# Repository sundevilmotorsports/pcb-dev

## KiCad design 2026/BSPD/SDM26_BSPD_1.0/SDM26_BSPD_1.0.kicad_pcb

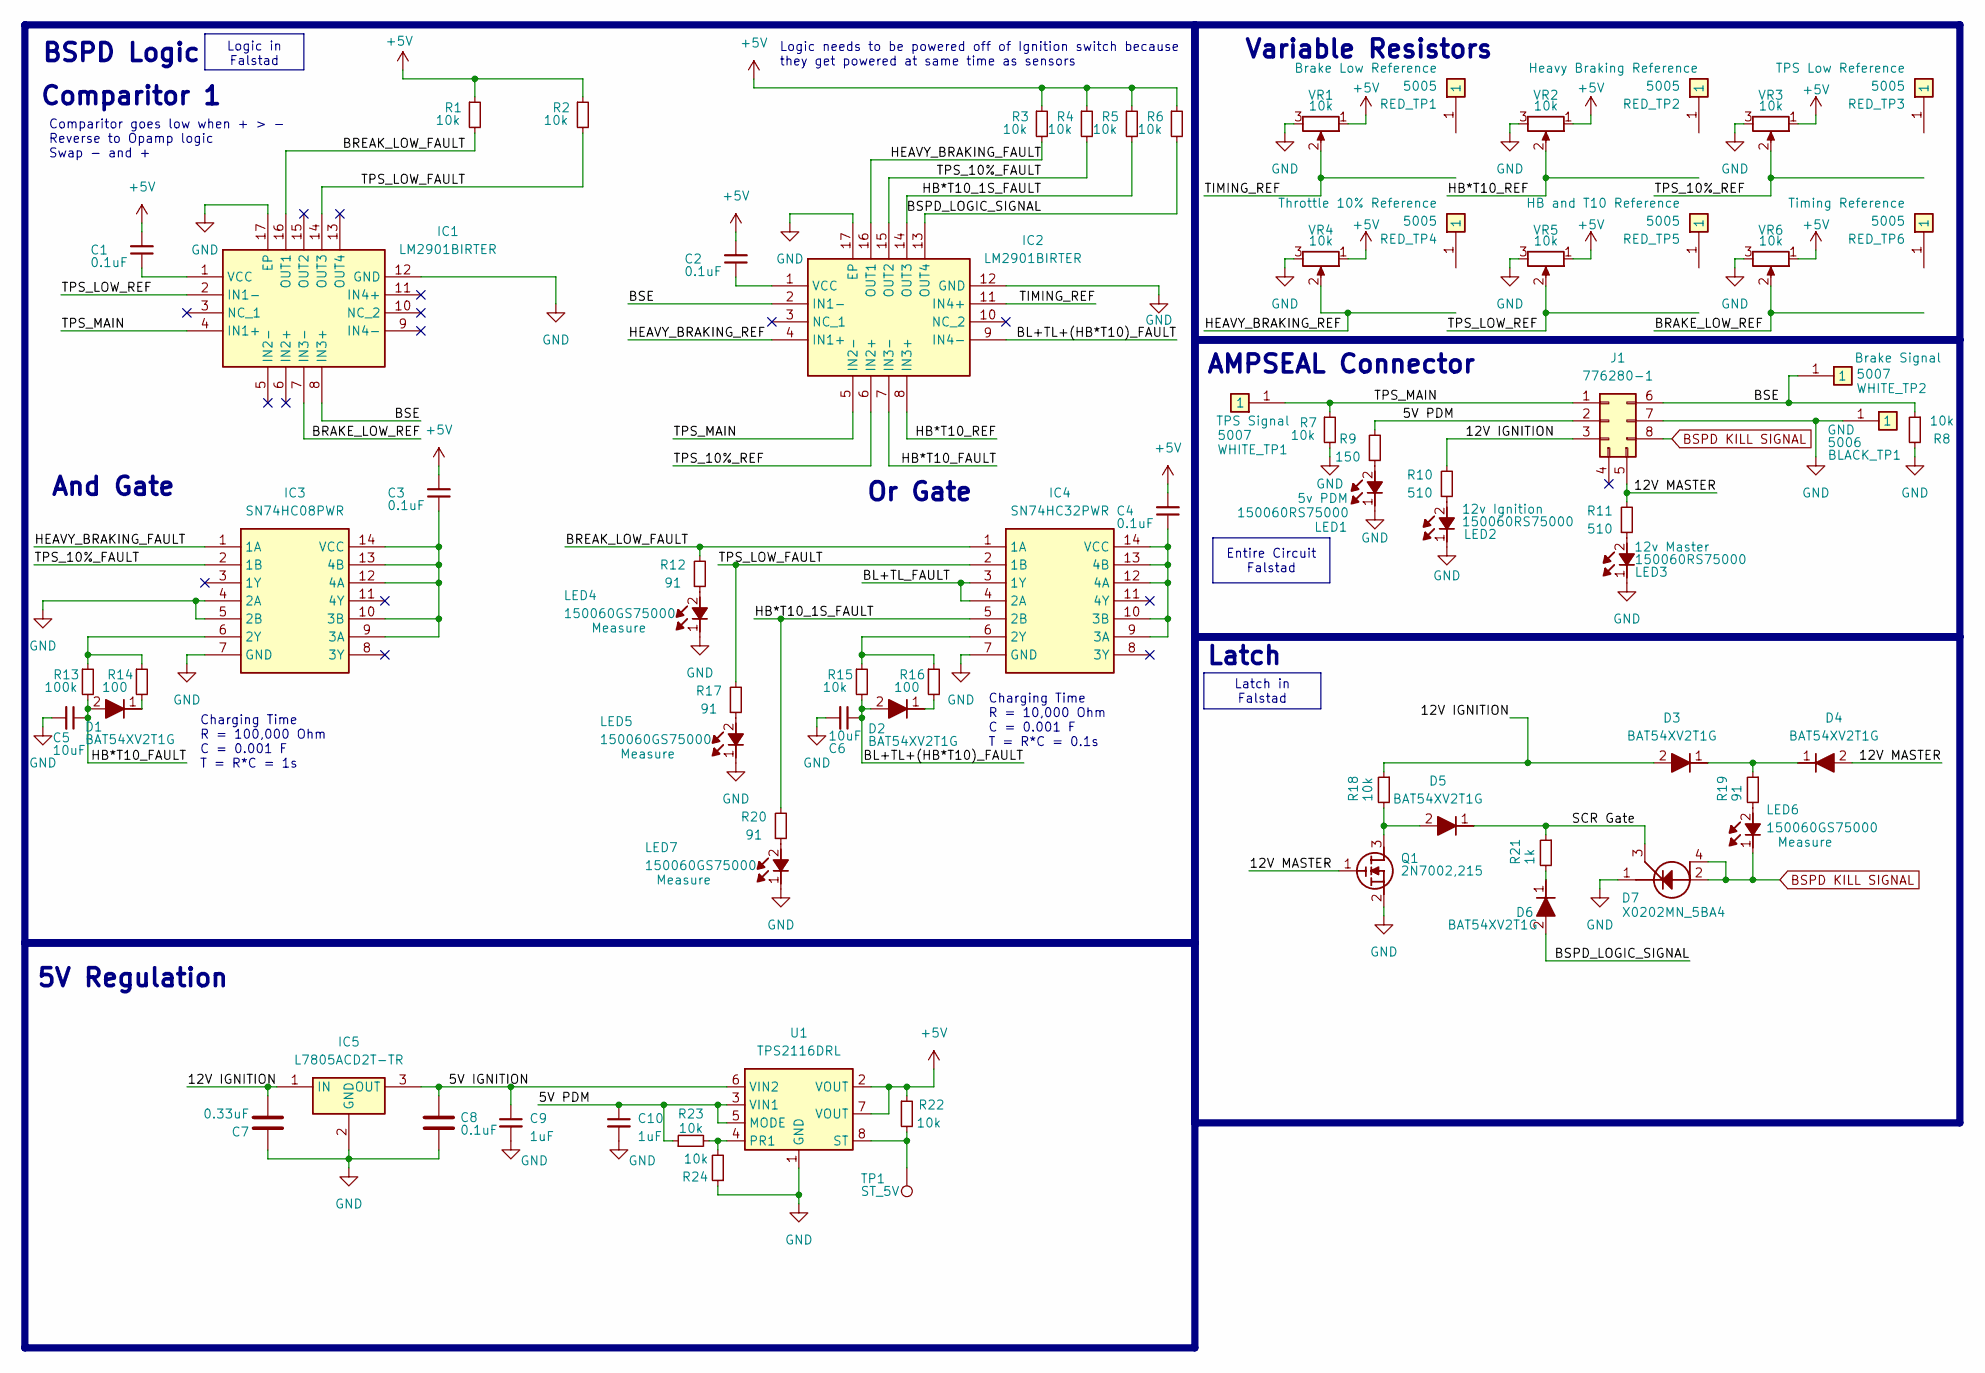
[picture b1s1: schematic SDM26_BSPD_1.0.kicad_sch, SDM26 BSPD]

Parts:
BLACK_TP1: 5006; Mouser Part Number 534-5006
C1, C2, C3, C4, C8: 0.1uF; C_0603_1608Metric
C5, C6: 10uF; C_0603_1608Metric
C7: 0.33uF; C_0603_1608Metric
C9, C10: 1uF; C_0603_1608Metric
D1, D2, D3, D4, D5, D6: BAT54XV2T1G; SODFL1608X70N; Mouser Part Number 863-BAT54XV2T1G
D7: X0202MN_5BA4; SOT230P700X190-4N; Mouser Part Number 511-X0202MN
IC1, IC2: LM2901BIRTER; QFN50P300X300X80-17N-D; Mouser Part Number 595-LM2901BIRTER
IC3: SN74HC08PWR; SOP65P640X120-14L; Mouser Part Number 595-SN74HC08PWR
IC4: SN74HC32PWR; SOP65P640X120-14L; Mouser Part Number 595-SN74HC32PWR
IC5: L7805ACD2T-TR; L7805ACD2TTR; Mouser Part Number 511-L7805ACD2T-TR
J1: 776280-1; Mouser Part Number 571-776280-1
LED1, LED2, LED3: 150060RS75000; LEDC1608X80N; Mouser Part Number 710-150060RS75000
LED4, LED5, LED6, LED7: 150060GS75000; LEDC1608X80N; Mouser Part Number 710-150060GS75000
Q1: 2N7002,215; SOT95P230X110-3N; Mouser Part Number 771-2N7002-T/R
R1, R2, R3, R4, R5, R6, R7, R8, R15, R18, R22, R23, R24: 10k; R_0603_1608Metric
R9: 150; R_0603_1608Metric
R10, R11: 510; R_0603_1608Metric
R12, R17, R19, R20: 91; R_0603_1608Metric
R13: 100k; R_0603_1608Metric
R14, R16: 100; R_0603_1608Metric
R21: 1k; R_0603_1608Metric
RED_TP1, RED_TP2, RED_TP3, RED_TP4, RED_TP5, RED_TP6: 5005; Mouser Part Number 534-5005
TP1: ST_5V; TestPoint_Pad_1.5x1.5mm
U1: TPS2116DRL; SOT-583-8
VR1, VR2, VR3, VR4, VR5, VR6: 10k; 3386P1103TLF; Mouser Part Number 652-3386P-1-103TLF
WHITE_TP1, WHITE_TP2: 5007; Mouser Part Number 534-5007

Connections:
+5V: C1.2, C2.2, C3.2, C4.2, R1.1, R2.1, R3.1, R4.1, R5.1, R6.1, R22.1, U1.2 (VOUT), U1.7 (VOUT), VR1.1 (CCW), VR2.1 (CCW), VR3.1 (CCW), VR4.1 (CCW), VR5.1 (CCW), VR6.1 (CCW)
/5V IGNITION: C8.2, C9.1, IC5.3 (OUT), U1.6 (VIN2)
/5V PDM: C10.1, J1.2, R9.2, R23.1, U1.3 (VIN1), U1.5 (MODE)
/12V IGNITION: C7.2, D3.2 (A), IC5.1 (IN), J1.3, R10.2, R18.1
/12V MASTER: D4.2 (A), J1.5, Q1.1 (G), R11.2
/BL+TL+(HB*T10)_FAULT: C6.1, D2.2 (A), IC2.9 (IN4-), R15.2
/BL+TL_FAULT: IC4.3 (1Y), IC4.4 (2A)
/BRAKE_LOW_REF: IC1.7 (IN3-), VR6.2 (Wiper)
/BREAK_LOW_FAULT: IC1.16 (OUT1), IC4.1 (1A), R1.2, R12.2
/BSE: IC1.8 (IN3+), IC2.2 (IN1-), J1.6, R8.1, WHITE_TP2.1
/BSPD_LOGIC_SIGNAL: D6.2 (A), IC2.13 (OUT4), R6.2
/HB*T10_1S_FAULT: IC2.14 (OUT3), IC4.5 (2B), R5.2, R20.2
/HB*T10_FAULT: C5.1, D1.2 (A), IC2.7 (IN3-), R13.2
/HB*T10_REF: IC2.8 (IN3+), VR2.2 (Wiper)
/HEAVY_BRAKING_FAULT: IC2.16 (OUT1), IC3.1 (1A), R3.2
/HEAVY_BRAKING_REF: IC2.4 (IN1+), VR4.2 (Wiper)
/SCR Gate: D5.1 (K), D7.3 (G), R21.1
/TIMING_REF: IC2.11 (IN4+), VR1.2 (Wiper)
/TPS_10%_FAULT: IC2.15 (OUT2), IC3.2 (1B), R4.2
/TPS_10%_REF: IC2.6 (IN2+), VR3.2 (Wiper)
/TPS_LOW_FAULT: IC1.14 (OUT3), IC4.2 (1B), R2.2, R17.2
/TPS_LOW_REF: IC1.2 (IN1-), VR5.2 (Wiper)
/TPS_MAIN: IC1.4 (IN1+), IC2.5 (IN2-), J1.1, R7.1, WHITE_TP1.1
BSPD KILL SIGNAL: D7.2 (A_1), D7.4 (A_2), J1.8, LED6.1 (K)
GND: BLACK_TP1.1, C5.2, C6.2, C7.1, C8.1, C9.2, C10.2, D7.1 (K), IC1.12 (GND), IC1.17 (EP), IC2.12 (GND), IC2.17 (EP), IC3.4 (2A), IC3.5 (2B), IC3.7 (GND), IC4.7 (GND), IC5.2 (GND), J1.7, LED1.1 (K), LED2.1 (K), LED3.1 (K), LED4.1 (K), LED5.1 (K), LED7.1 (K), Q1.2 (S), R7.2, R8.2, R24.1, U1.1 (GND), VR1.3 (CW), VR2.3 (CW), VR3.3 (CW), VR4.3 (CW), VR5.3 (CW), VR6.3 (CW)
unnamed: D1.1 (K), R14.2
unnamed: D2.1 (K), R16.2
unnamed: D3.1 (K), D4.1 (K), R19.1
unnamed: D5.2 (A), Q1.3 (D), R18.2
unnamed: D6.1 (K), R21.2
unnamed: C1.1, IC1.1 (VCC)
unnamed: C2.1, IC2.1 (VCC)
unnamed: IC3.6 (2Y), R13.1, R14.1
unnamed: C3.1, IC3.9 (3A), IC3.10 (3B), IC3.12 (4A), IC3.13 (4B), IC3.14 (VCC)
unnamed: IC4.6 (2Y), R15.1, R16.1
unnamed: C4.1, IC4.9 (3A), IC4.10 (3B), IC4.12 (4A), IC4.13 (4B), IC4.14 (VCC)
unnamed: LED1.2 (A), R9.1
unnamed: LED2.2 (A), R10.1
unnamed: LED3.2 (A), R11.1
unnamed: LED4.2 (A), R12.1
unnamed: LED5.2 (A), R17.1
unnamed: LED6.2 (A), R19.2
unnamed: LED7.2 (A), R20.1
unnamed: R23.2, R24.2, U1.4 (PR1)
unnamed: R22.2, TP1.1, U1.8 (ST)

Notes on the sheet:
5V Regulation
Latch
And Gate
Comparitor goes low when + > - Reverse to Opamp logic Swap - and +
Variable Resistors
Logic needs to be powered off of Ignition switch because they get powered at same time as sensors
Charging Time R = 100,000 Ohm C = 0.001 F T = R*C = 1s
Charging Time R = 10,000 Ohm C = 0.001 F T = R*C = 0.1s
AMPSEAL Connector
BSPD Logic
Or Gate
Comparitor 1
Latch in Falstad
Entire Circuit Falstad
Logic in Falstad

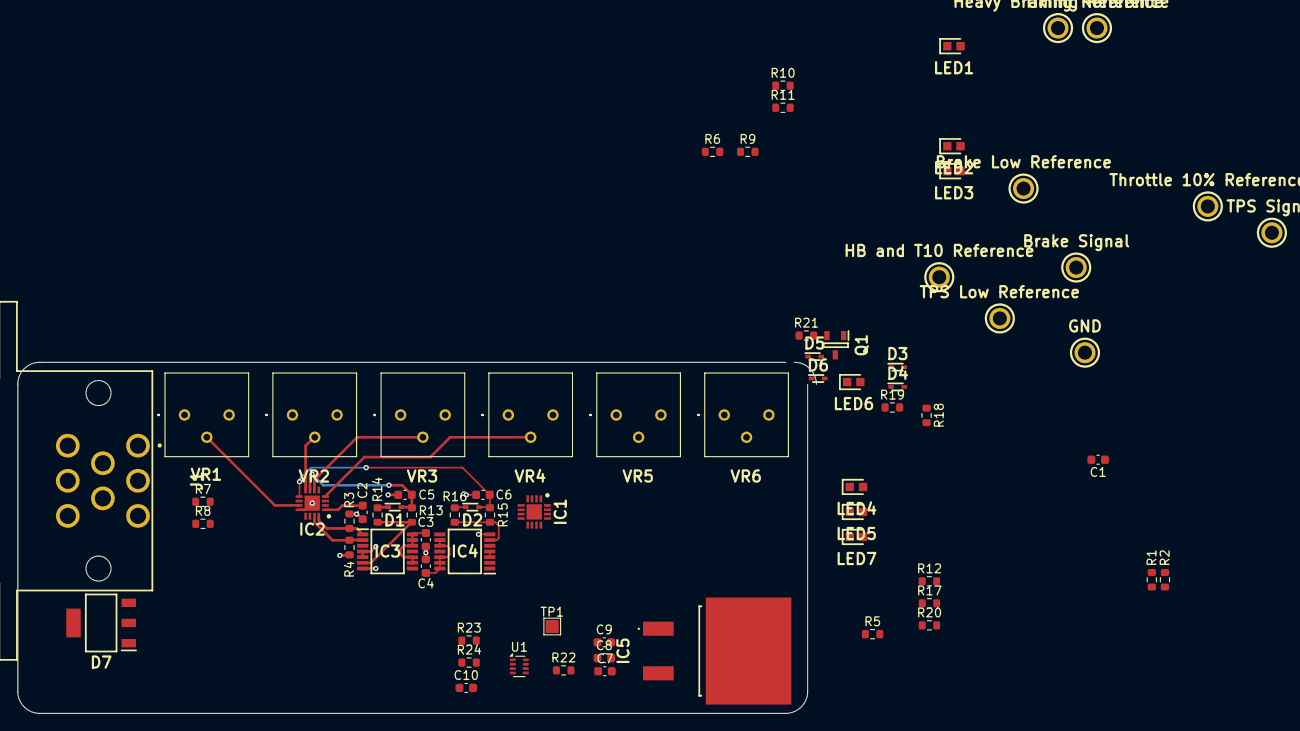
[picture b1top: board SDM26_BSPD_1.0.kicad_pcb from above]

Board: 4 copper layers, 91.0 x 40.0 mm, 72 parts (0 on the bottom side), 45 nets.

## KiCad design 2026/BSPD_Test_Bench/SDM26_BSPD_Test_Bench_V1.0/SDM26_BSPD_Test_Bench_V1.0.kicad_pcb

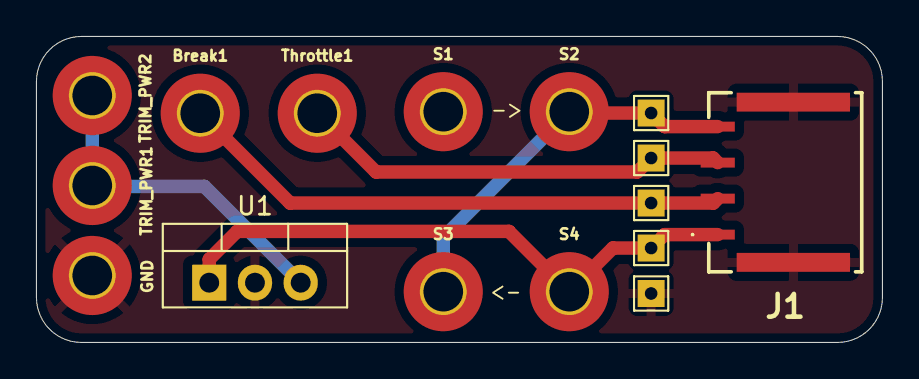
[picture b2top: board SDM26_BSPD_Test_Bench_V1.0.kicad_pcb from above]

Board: 2 copper layers, 47.0 x 17.0 mm, 11 parts (0 on the bottom side), 6 nets.

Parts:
Break1: MountingHole_Pad_MP; MountingHole_2.2mm_M2_Pad_TopBottom
GND: MountingHole_Pad_MP; MountingHole_2.2mm_M2_Pad_TopBottom
J1: SM04B-ULHK-1TA1-ETB_HF_; SM04BULHK1TA1ETBHF
S1, S2, S3, S4: MountingHole_Pad_MP; MountingHole_2.2mm_M2_Pad_TopBottom
TRIM_PWR1, TRIM_PWR2: MountingHole_Pad_MP; MountingHole_2.2mm_M2_Pad_TopBottom
Throttle1: MountingHole_Pad_MP; MountingHole_2.2mm_M2_Pad_TopBottom
U1: SPX2920U-5.0_TO220; TO-220-3_Vertical

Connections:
/Break: Break1.1, J1.2
/Throttle: J1.3, Throttle1.1
GND: GND.1, J1.5 (MP1), J1.6 (MP2), U1.2 (GND)
IGNPWR: J1.1, S4.1, U1.1 (VI)
MASTERPWR: J1.4, S2.1, S3.1
unnamed: TRIM_PWR1.1, TRIM_PWR2.1, U1.3 (VO)

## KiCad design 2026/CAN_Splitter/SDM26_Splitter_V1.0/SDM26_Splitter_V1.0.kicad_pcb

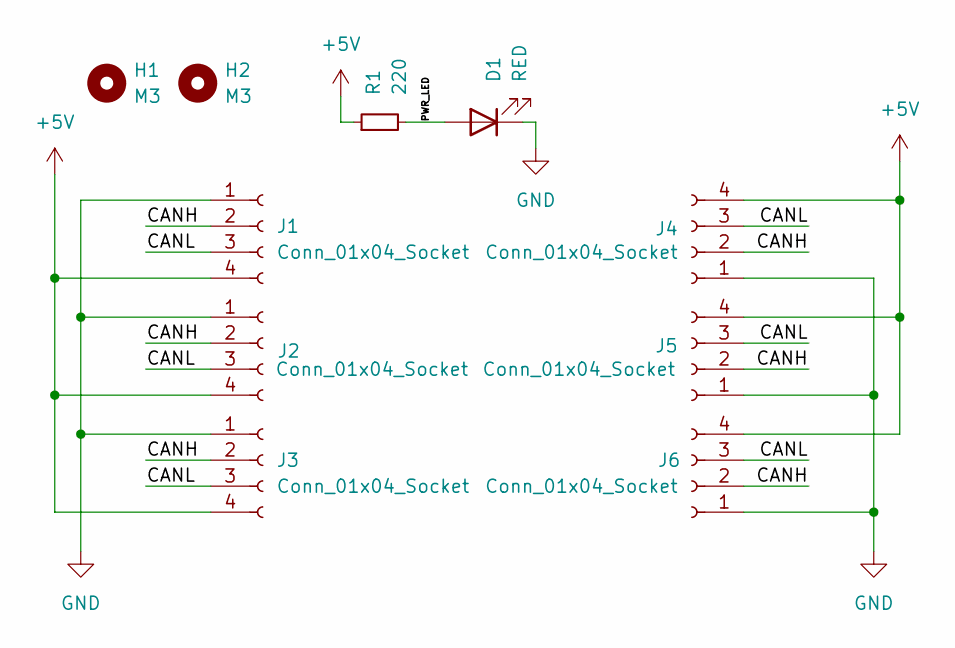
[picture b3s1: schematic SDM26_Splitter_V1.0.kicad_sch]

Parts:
D1: RED; LED_1206_3216Metric
H1, H2: M3; MountingHole_3.2mm_M3
J1, J2, J3, J4, J5, J6: Conn_01x04_Socket; JST_EH_S4B-EH_1x04_P2.50mm_Horizontal
R1: 220; C_0603_1608Metric

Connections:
+5V: J1.4, J2.4, J3.4, J4.4, J5.4, J6.4, R1.1
/CANH: J1.2, J2.2, J3.2, J4.2, J5.2, J6.2
/CANL: J1.3, J2.3, J3.3, J4.3, J5.3, J6.3
/PWR_LED: D1.2 (A), R1.2
GND: D1.1 (K), J1.1, J2.1, J3.1, J4.1, J5.1, J6.1

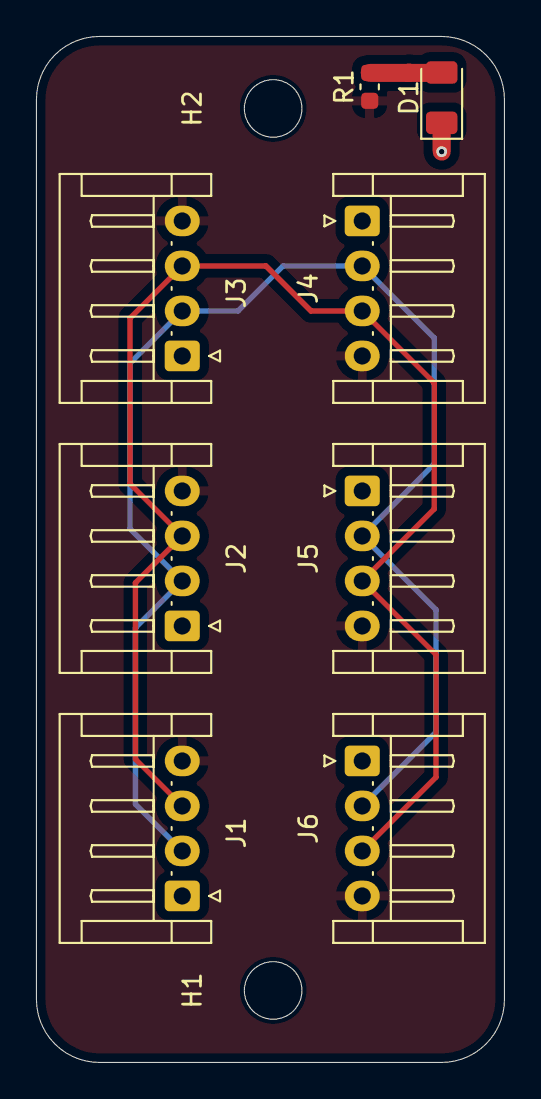
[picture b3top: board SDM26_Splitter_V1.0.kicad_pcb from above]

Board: 2 copper layers, 26.0 x 57.0 mm, 10 parts (0 on the bottom side), 5 nets.

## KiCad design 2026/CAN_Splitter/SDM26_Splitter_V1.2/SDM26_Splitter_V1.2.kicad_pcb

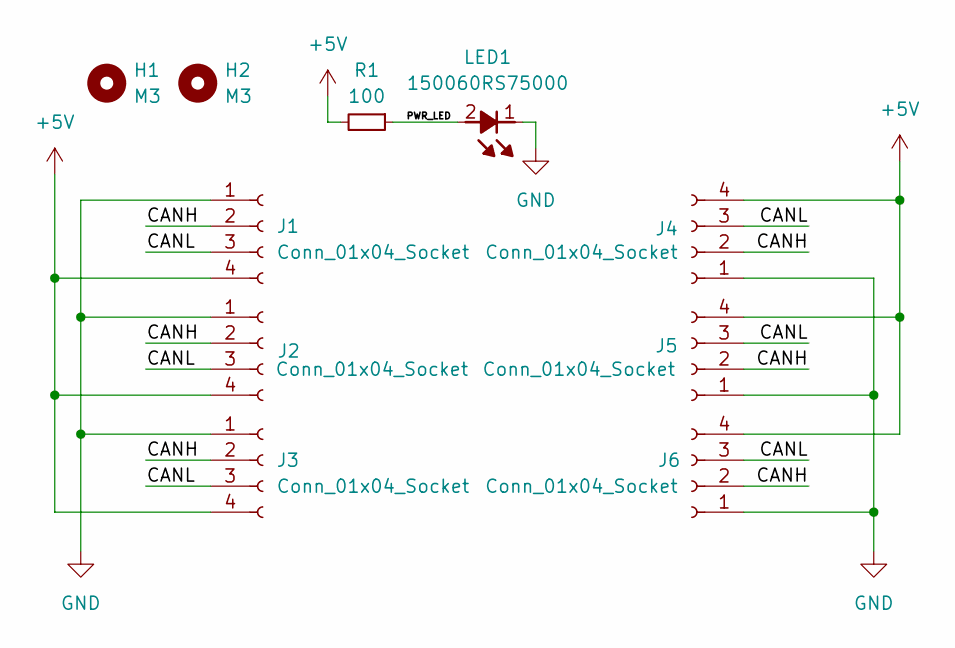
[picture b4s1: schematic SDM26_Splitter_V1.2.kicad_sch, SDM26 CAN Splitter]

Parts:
H1, H2: M3; MountingHole_3.2mm_M3
J1, J2, J3, J4, J5, J6: Conn_01x04_Socket; JST_EH_S4B-EH_1x04_P2.50mm_Horizontal_1
LED1: 150060RS75000; LEDC1608X80N; Mouser Part Number 710-150060RS75000
R1: 100; C_0603_1608Metric

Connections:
+5V: J1.4, J2.4, J3.4, J4.4, J5.4, J6.4, R1.2
/CANH: J1.2, J2.2, J3.2, J4.2, J5.2, J6.2
/CANL: J1.3, J2.3, J3.3, J4.3, J5.3, J6.3
/PWR_LED: LED1.2 (A), R1.1
GND: J1.1, J2.1, J3.1, J4.1, J5.1, J6.1, LED1.1 (K)

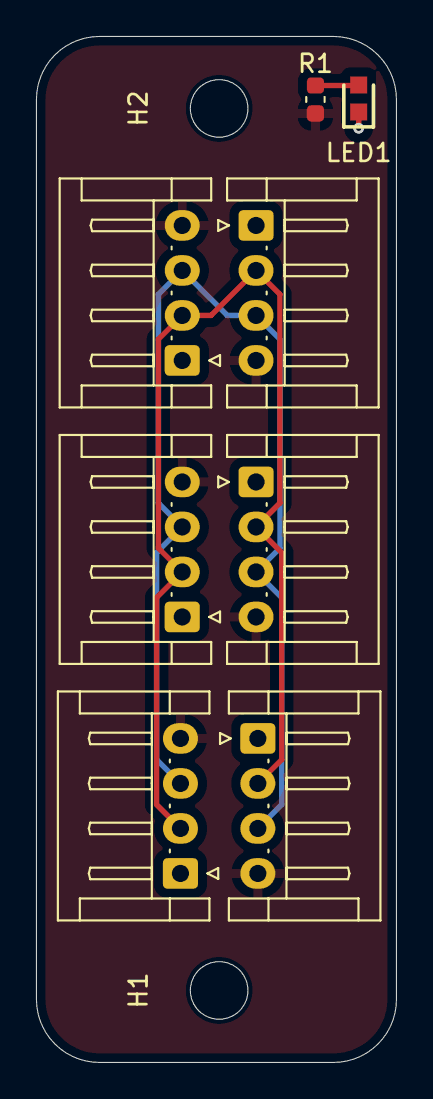
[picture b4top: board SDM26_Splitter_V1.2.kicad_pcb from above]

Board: 2 copper layers, 20.0 x 57.0 mm, 10 parts (0 on the bottom side), 5 nets.

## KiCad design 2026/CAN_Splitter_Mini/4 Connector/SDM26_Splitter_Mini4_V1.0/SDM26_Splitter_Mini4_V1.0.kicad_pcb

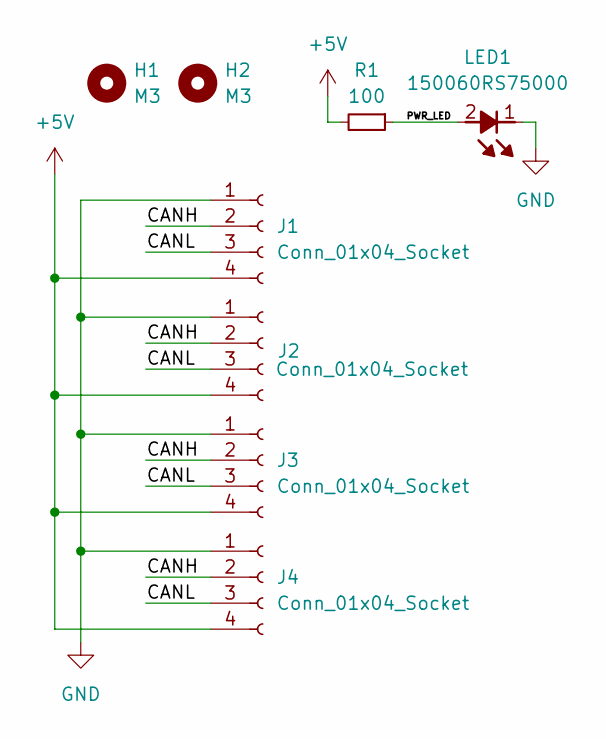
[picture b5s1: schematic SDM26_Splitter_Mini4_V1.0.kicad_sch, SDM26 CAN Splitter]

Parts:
H1, H2: M3; MountingHole_3.2mm_M3
J1, J2, J3, J4: Conn_01x04_Socket; JST_EH_S4B-EH_1x04_P2.50mm_Horizontal_1
LED1: 150060RS75000; LEDC1608X80N; Mouser Part Number 710-150060RS75000
R1: 100; C_0603_1608Metric

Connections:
+5V: J1.4, J2.4, J3.4, J4.4, R1.2
/CANH: J1.2, J2.2, J3.2, J4.2
/CANL: J1.3, J2.3, J3.3, J4.3
/PWR_LED: LED1.2 (A), R1.1
GND: J1.1, J2.1, J3.1, J4.1, LED1.1 (K)

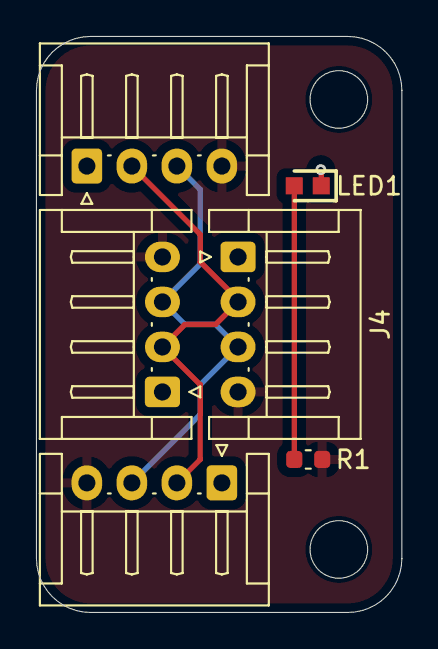
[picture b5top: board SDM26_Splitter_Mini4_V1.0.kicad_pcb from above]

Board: 2 copper layers, 20.3 x 32.0 mm, 8 parts (0 on the bottom side), 5 nets.

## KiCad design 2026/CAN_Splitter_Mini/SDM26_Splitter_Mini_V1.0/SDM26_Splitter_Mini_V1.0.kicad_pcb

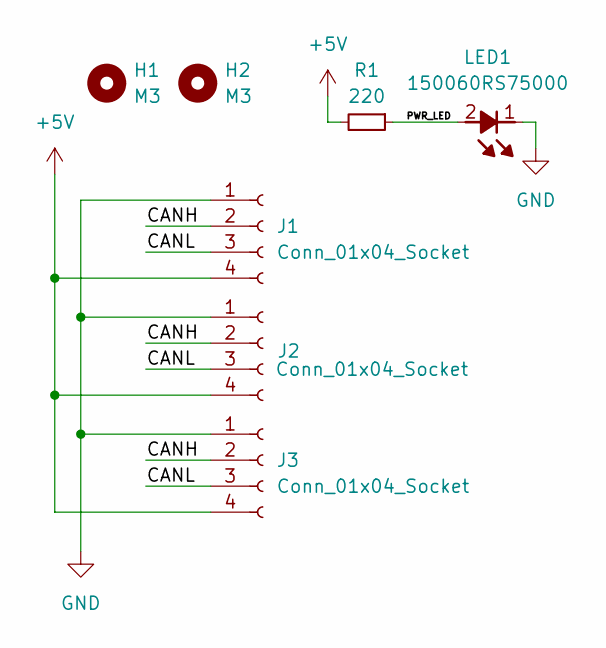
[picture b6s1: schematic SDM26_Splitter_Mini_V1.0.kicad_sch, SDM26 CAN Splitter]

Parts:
H1, H2: M3; MountingHole_3.2mm_M3
J1, J2, J3: Conn_01x04_Socket; JST_EH_S4B-EH_1x04_P2.50mm_Horizontal
LED1: 150060RS75000; LEDC1608X80N; Mouser Part Number 710-150060RS75000
R1: 220; C_0603_1608Metric

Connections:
+5V: J1.4, J2.4, J3.4, R1.2
/CANH: J1.2, J2.2, J3.2
/CANL: J1.3, J2.3, J3.3
/PWR_LED: LED1.2 (A), R1.1
GND: J1.1, J2.1, J3.1, LED1.1 (K)

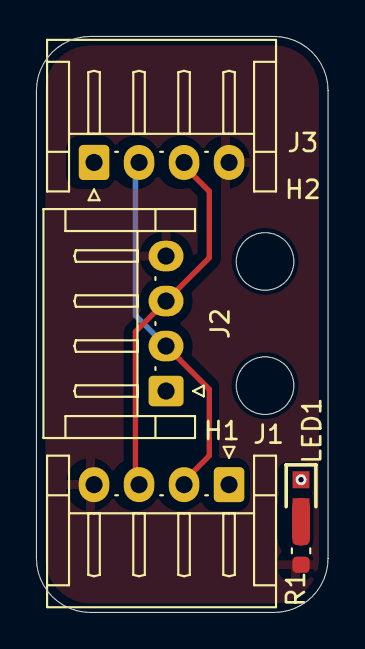
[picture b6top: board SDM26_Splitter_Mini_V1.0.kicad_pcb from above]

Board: 2 copper layers, 16.2 x 32.0 mm, 7 parts (0 on the bottom side), 5 nets.
